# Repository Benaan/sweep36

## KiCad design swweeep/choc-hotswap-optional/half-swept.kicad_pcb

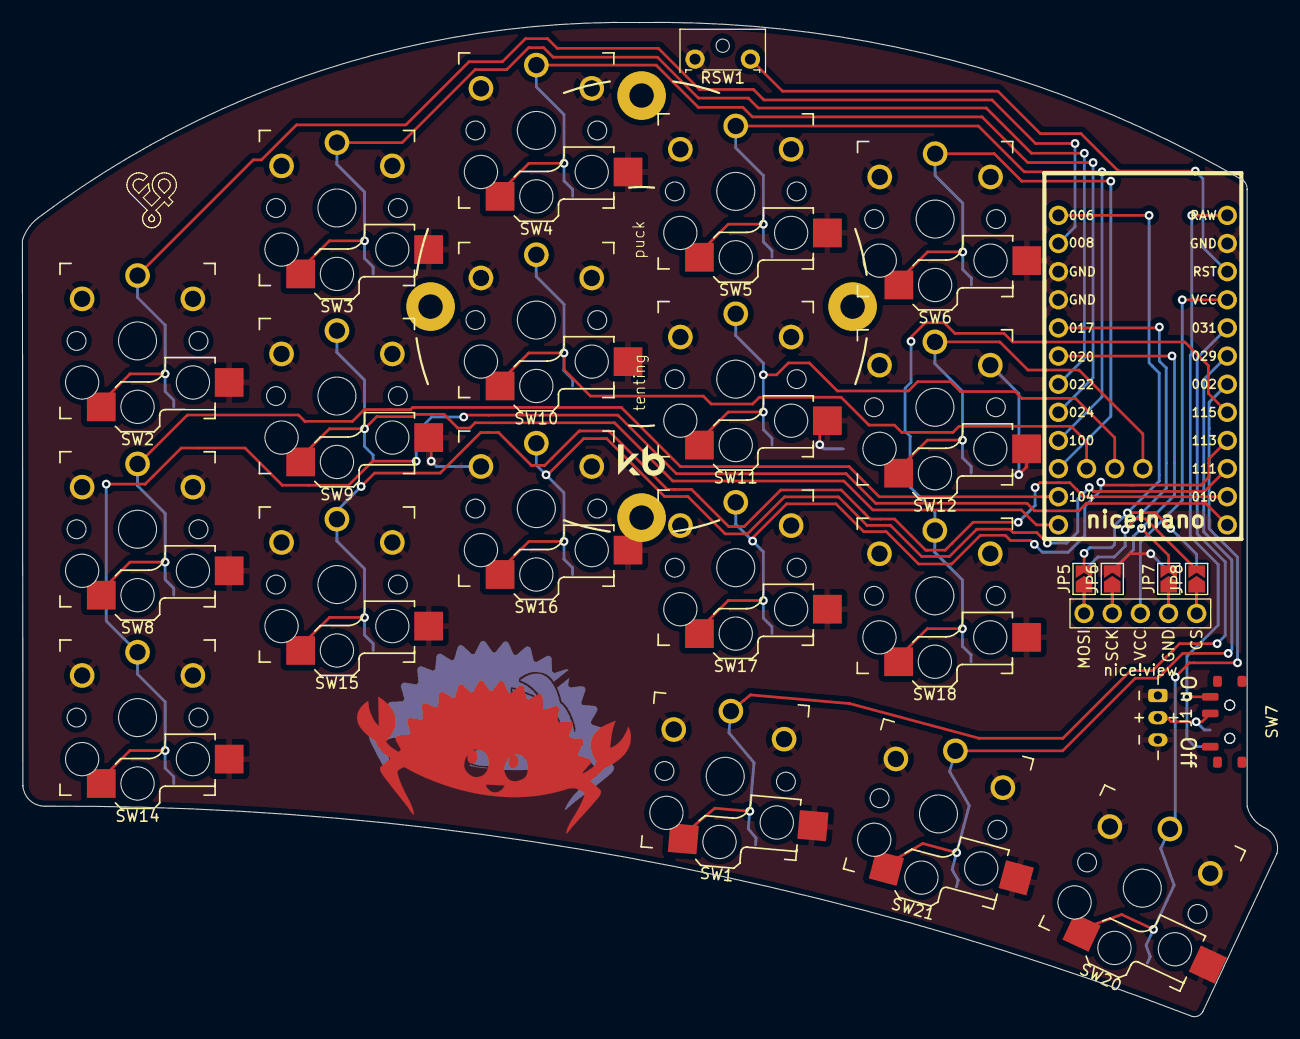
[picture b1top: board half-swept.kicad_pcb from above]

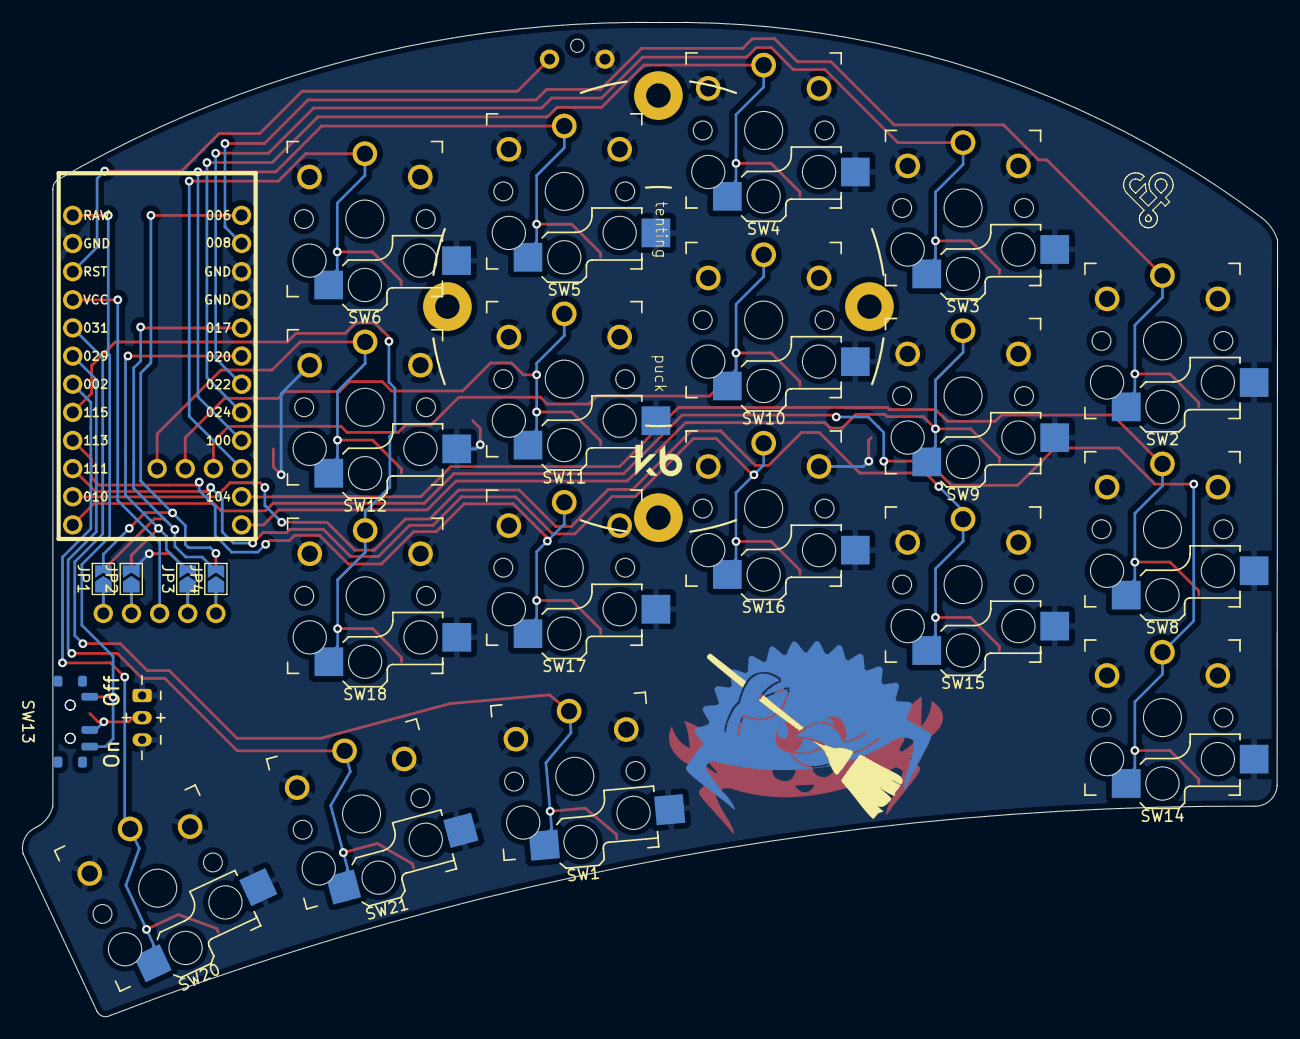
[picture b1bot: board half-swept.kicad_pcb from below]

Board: 2 copper layers, 113.3 x 89.7 mm, 32 parts (5 on the bottom side), 30 nets.

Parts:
Display1: nice!view; nice_view
J1: JST-BATTERY; JST_PH_S3B-PH-K-keyboard
JP1, JP2, JP3, JP4, JP5, JP6, JP7, JP8: Jumper_2_Open; SolderJumper-2_P1.3mm_Open_TrianglePad1.0x1.5mm
RSW1: SW_Push; SW_Tactile_SPST_Angled_MJTP1117-no-mount
SW1, SW2, SW3, SW4, SW5, SW6, SW8, SW9, SW10, SW11, SW12, SW14, SW15, SW16, SW17, SW18, SW20, SW21: SW_Push; Kailh_socket_PG1350_optional_reversible_millmax
SW7, SW13: SW_DPDT; MSK-12C02
U1: nice_nano

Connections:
unnamed: Display1.1 (MOSI), JP4.1 (A), JP5.1 (A)
unnamed: Display1.2 (SCK), JP3.1 (A), JP6.1 (A)
unnamed: Display1.4 (GND), JP2.1 (A), JP7.1 (A)
unnamed: Display1.5 (CS), JP1.1 (A), JP8.1 (A)
unnamed: J1.2, SW7.2 (B), SW13.2 (B)
Switch1: SW2.1, U1.2 (RX1/P0.08)
Switch2: SW3.1, U1.7 (P0.22)
Switch3: SW4.1, U1.8 (P0.24)
Switch4: SW5.1, U1.9 (P1.00)
Switch5: SW6.1, U1.10 (P0.11)
Switch6: SW8.1, U1.11 (P1.04)
Switch7: SW9.1, U1.12 (P1.06)
Switch8: SW10.1, U1.31 (P1.01)
Switch9: SW11.1, U1.32 (P1.02)
Switch10: SW12.1, U1.33 (P1.07)
Switch11: SW14.1, U1.13 (NFC1/P0.09)
Switch12: SW15.1, U1.14 (NFC2/P0.10)
Switch13: SW16.1, U1.15 (P1.11)
Switch14: SW17.1, U1.16 (P1.13)
Switch15: SW18.1, U1.17 (P1.15)
Switch16: SW20.1, U1.18 (AIN0/P0.02)
Switch17: SW21.1, U1.19 (AIN5/P0.29)
Switch18: SW1.1, U1.20 (AIN7/P0.31)
gnd: J1.1, J1.3, JP2.2 (B), JP6.2 (B), RSW1.1, SW1.2, SW2.2, SW3.2, SW4.2, SW5.2, SW6.2, SW8.2, SW9.2, SW10.2, SW11.2, SW12.2, SW14.2, SW15.2, SW16.2, SW17.2, SW18.2, SW20.2, SW21.2, U1.3 (GND), U1.4 (GND), U1.23 (GND)
mosi: JP4.2 (B), JP8.2 (B), U1.5 (P0.17)
nv_cs: JP1.2 (B), JP5.2 (B), U1.1 (TX0/P0.06)
raw: SW7.3 (C), SW13.3 (C), U1.24 (BATIN/P0.04)
reset: RSW1.2, U1.22 (RST)
sck: JP3.2 (B), JP7.2 (B), U1.6 (P0.20)
vcc: Display1.3 (VCC), U1.21 (VCC)

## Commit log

2023-07-28 Revert "replaced on off switch, from MSK12C02 to OS102011MA1QN1"
    This reverts commit 761ca253cc3f7c0a016fc91ec44eaa0a86f70d5a.
2023-07-28 added ferris
